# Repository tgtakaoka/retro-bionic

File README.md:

<div align="center">

# retro-bionic

**Run real vintage CPUs on a modern Cortex-M7 — with a debugger, assembler and disassembler built in.**

</div>

## Contents

- [CPUs](docs/supported-cpus.md) — every target supported and planned, with the variants each detects
- [Hardware](docs/hardware.md) — the board stack, signal naming and the awkward chips
- [3.3 V base](docs/3v3-base.md) — planned second base board, its keying and what it unlocks
- [Debugger](docs/debugger.md) — full command reference
- [Build & run](docs/build.md) — toolchain, flashing, serial ports
- [Samples](docs/samples.md) — the programs and how to run them
- [CPU speed by an assembly-language Mandelbrot](docs/mandelbrot.md) — the benchmark's seconds per frame on each chip
- [Demos](docs/demos.md) — recorded terminal sessions, and what to watch for in them

## What is this?

Put a real MC6809, Z80, TMS9900 or CDP1802 into a ZIF socket and single-step it, one bus
cycle at a time, from a terminal on your desk.

**Bionic** runs *genuine* vintage processors — not emulations of them. A
[Teensy 4.1](https://www.pjrc.com/store/teensy41.html) is wired to every pin of the target
CPU and drives the whole system around it: the clock, every bus cycle, and the memory and
peripherals the chip thinks it is talking to. One firmware image — about 470 kB including
every assembler, disassembler and debugger — covers all **57 supported targets**, and the
board tells the controller which one it is.

<div align="center">

</div>

The hardware is two boards:

1. **Base** — the Teensy 4.1, five TXS0108E level shifters for 3.3 V ↔ 5 V translation, data
   bus holders, the 48-pin ZIF socket and the HALT/RUN switch.
2. **CPU adapter** — one small board per processor, holding little more than the chip
   itself, its identity EEPROM and whatever power the part demands. The TMS9900 board, for
   example, generates its own +12 V and −5 V rails and a non-overlapping four-phase clock, and CPUs with
   large address spaces carry an address bus multiplexer.

The 48 signals crossing the connector are named `P10`–`P57`, and each CPU board maps them to
its own pinout in a small TOML file. See **[docs/hardware.md](docs/hardware.md)**.

## Debugger features

- **Single-step a physical CPU** and print every bus cycle it performed (`S`).
- **Live disassembly** of the next instruction after each register dump, via
  [libasm](https://github.com/tgtakaoka/libasm).
- **Registers** read back by injecting instructions and capturing the resulting cycles —
  read and write them (`r`, `=`).
- **Breakpoints**, up to 4 plus one temporary for run-until-address (`B`, `b`, `g`).
- **Memory** dump and patch, separate program and data spaces for Harvard architectures
  (`d`, `p`, `m`, `M`), plus a write-protect area on targets that need one (`P`).
- **Upload** Intel HEX or Motorola S-record straight over the serial link (`U`).
- **Emulated peripherals** — MC6850 ACIA and i8251 USART — and on-chip serial ports of MCU
  targets bridged to your terminal (`I`).
- **Disk images on the SD card** behind emulated disk controllers (`L`, `O`), enough to
  boot [CP/M 2.2, CP/M-86, CP/M-68K, NitrOS-9, Unix V6 and 2.11BSD](docs/samples.md#operating-systems).
- **Automatic board identification** from a UNI/O serial EEPROM, plus **runtime variant
  detection**: one 6502 board reports `MOS6502`, `G65SC02`, `R65C02`, `W65C02S` or
  `W65C816S` depending on which die actually responds.

<div align="center">

<br><em>A <a href="samples/tms9900/mandelbrot.cast">real TMS9900 session</a>: registers,
disassembly, single-stepping with the bus trace, then drawing the Mandelbrot set.</em>
</div>

## Supported CPUs

All 58 targets, grouped by vendor and architecture:

<table>
<thead>
<tr><th>Vendor</th><th>Architecture</th><th>Targets</th></tr>
</thead>
<tbody>
<tr><td rowspan="6">Motorola</td><td>6800</td><td>MC6800 <em>MB8861</em>, MC6801 <em>HD6301</em>, MC6802 <em>MB8870</em>, MC68HC11A, MC68HC11D</td></tr>
<tr><td>6805</td><td>MC146805E2, MC68HC05C0, MC68HC08AZ0</td></tr>
<tr><td>6809</td><td>MC6809 <em>HD6309</em>, MC6809E <em>HD6309E</em></td></tr>
<tr><td>68HC12</td><td>MC68HC12B, MC9S12D, MC9S12X</td></tr>
<tr><td>68HC16</td><td>MC68HC16Z</td></tr>
<tr><td>68000</td><td>MC68008P, MC68008FN, MC68000P <em>MC68HC000, MC68010</em>, MC68000FN <em>MC68HC001, MC68010</em></td></tr>
<tr><td>MOS Technology</td><td>6502</td><td>MOS6502 <em>G65SC02, R65C02, W65C02S, W65C816S</em></td></tr>
<tr><td rowspan="6">Zilog</td><td>Z80</td><td>Z80, NSC800, KL5C80A12</td></tr>
<tr><td>Z180</td><td>Z180, HD64180S</td></tr>
<tr><td>Z280</td><td>Z280</td></tr>
<tr><td>Z380</td><td>Z380</td></tr>
<tr><td>Z8000</td><td>Z8001, Z8002</td></tr>
<tr><td>Z8</td><td>Z86C91, Z88C00</td></tr>
<tr><td rowspan="5">Intel</td><td>MCS-48</td><td>P8039 <em>MSM80C39</em></td></tr>
<tr><td>MCS-51</td><td>P8051 <em>P80C51</em></td></tr>
<tr><td>MCS-80/85</td><td>P8080, P8085</td></tr>
<tr><td>x86</td><td>P8086 <em>P8088, V30, V20</em>, D8087</td></tr>
<tr><td>MCS-96</td><td>P8095BH, N8097BH, S80C196KC, S80296SA</td></tr>
<tr><td rowspan="4">Texas Instruments</td><td>TMS9900</td><td>TMS9900, TMS9980, TMS9981, TMS9995, TMS99105 <em>TMS99110</em></td></tr>
<tr><td>TMS7000</td><td>TMS7000 <em>TMS7001, TMS7001NL4, TMS7002, TMS70C00, TMS70C02</em></td></tr>
<tr><td>TMS370</td><td>TMS370Cx5x</td></tr>
<tr><td>TMS320</td><td>TMS320C15</td></tr>
<tr><td rowspan="2">DEC</td><td>PDP-8</td><td>IM6100, HD6120</td></tr>
<tr><td>PDP-11</td><td>DCT11, DCJ11</td></tr>
<tr><td>RCA</td><td>COSMAC</td><td>CDP1802 <em>CDP1804A</em></td></tr>
<tr><td>Fairchild</td><td>F8</td><td>F3850</td></tr>
<tr><td rowspan="2">National</td><td>SC/MP II</td><td>INS8060</td></tr>
<tr><td>SC/MP III</td><td>INS8070</td></tr>
<tr><td>Signetics</td><td>2650</td><td>SCN2650</td></tr>
<tr><td>Toshiba</td><td>TLCS-90</td><td>TMP90C802</td></tr>
<tr><td>Hitachi</td><td>H16</td><td>HD641016</td></tr>
<tr><td>Panafacom</td><td>MN1610</td><td>MN1613 <em>MN1613A</em></td></tr>
<tr><td>General Instrument</td><td>CP1600</td><td>CP1610</td></tr>
</tbody>
</table>

Targets in *italics* are variants the firmware identifies at runtime, by executing
instructions that behave differently on each die — not by anything written on the board.

See **[docs/supported-cpus.md](docs/supported-cpus.md)** for the full table, including the
CPUs still to be supported.

## Repository layout

| Path | Contents |
|---|---|
| [`debugger/`](debugger) | Teensy 4.1 firmware — shared framework plus 30 per-family back ends |
| [`schematics/`](schematics) | KiCad projects: base, mezzanine, PLCC adapter and 54 CPU adapter boards, with gerbers and PDFs |
| [`pinout/`](pinout) | Pin-map definitions consumed by [dip](https://github.com/tgtakaoka/dip) |
| [`samples/`](samples) | Test programs — Mandelbrot, arithmetic suites, serial echo — ported to every CPU |
| [`scripts/`](scripts) | Bench control, regression, cycle recording and timing scripts, and the PlatformIO `compile_commands.json` helper |

## Related projects

| Project | Role |
|---|---|
| [**libasm**](https://github.com/tgtakaoka/libasm) | The assembler and disassembler engine — 41 architectures, 119 CPU variants, small enough to run on an AVR |
| [**libcli**](https://github.com/tgtakaoka/libcli) | The serial command-line front end the debugger is built on |
| [**dip**](https://github.com/tgtakaoka/dip) | Draws the pinout diagrams from the TOML files in [`pinout/`](pinout) |

## Resources

- **Recorded sessions** — [asciinema.org/~tgtakaoka](https://asciinema.org/~tgtakaoka)
- **Progress log** — [Bluesky](https://bsky.app/profile/tgtakaoka.bsky.social) ·
  [X](https://x.com/tgtakaoka)

## License

Licensed under the [Apache License, Version 2.0](LICENSE.md).

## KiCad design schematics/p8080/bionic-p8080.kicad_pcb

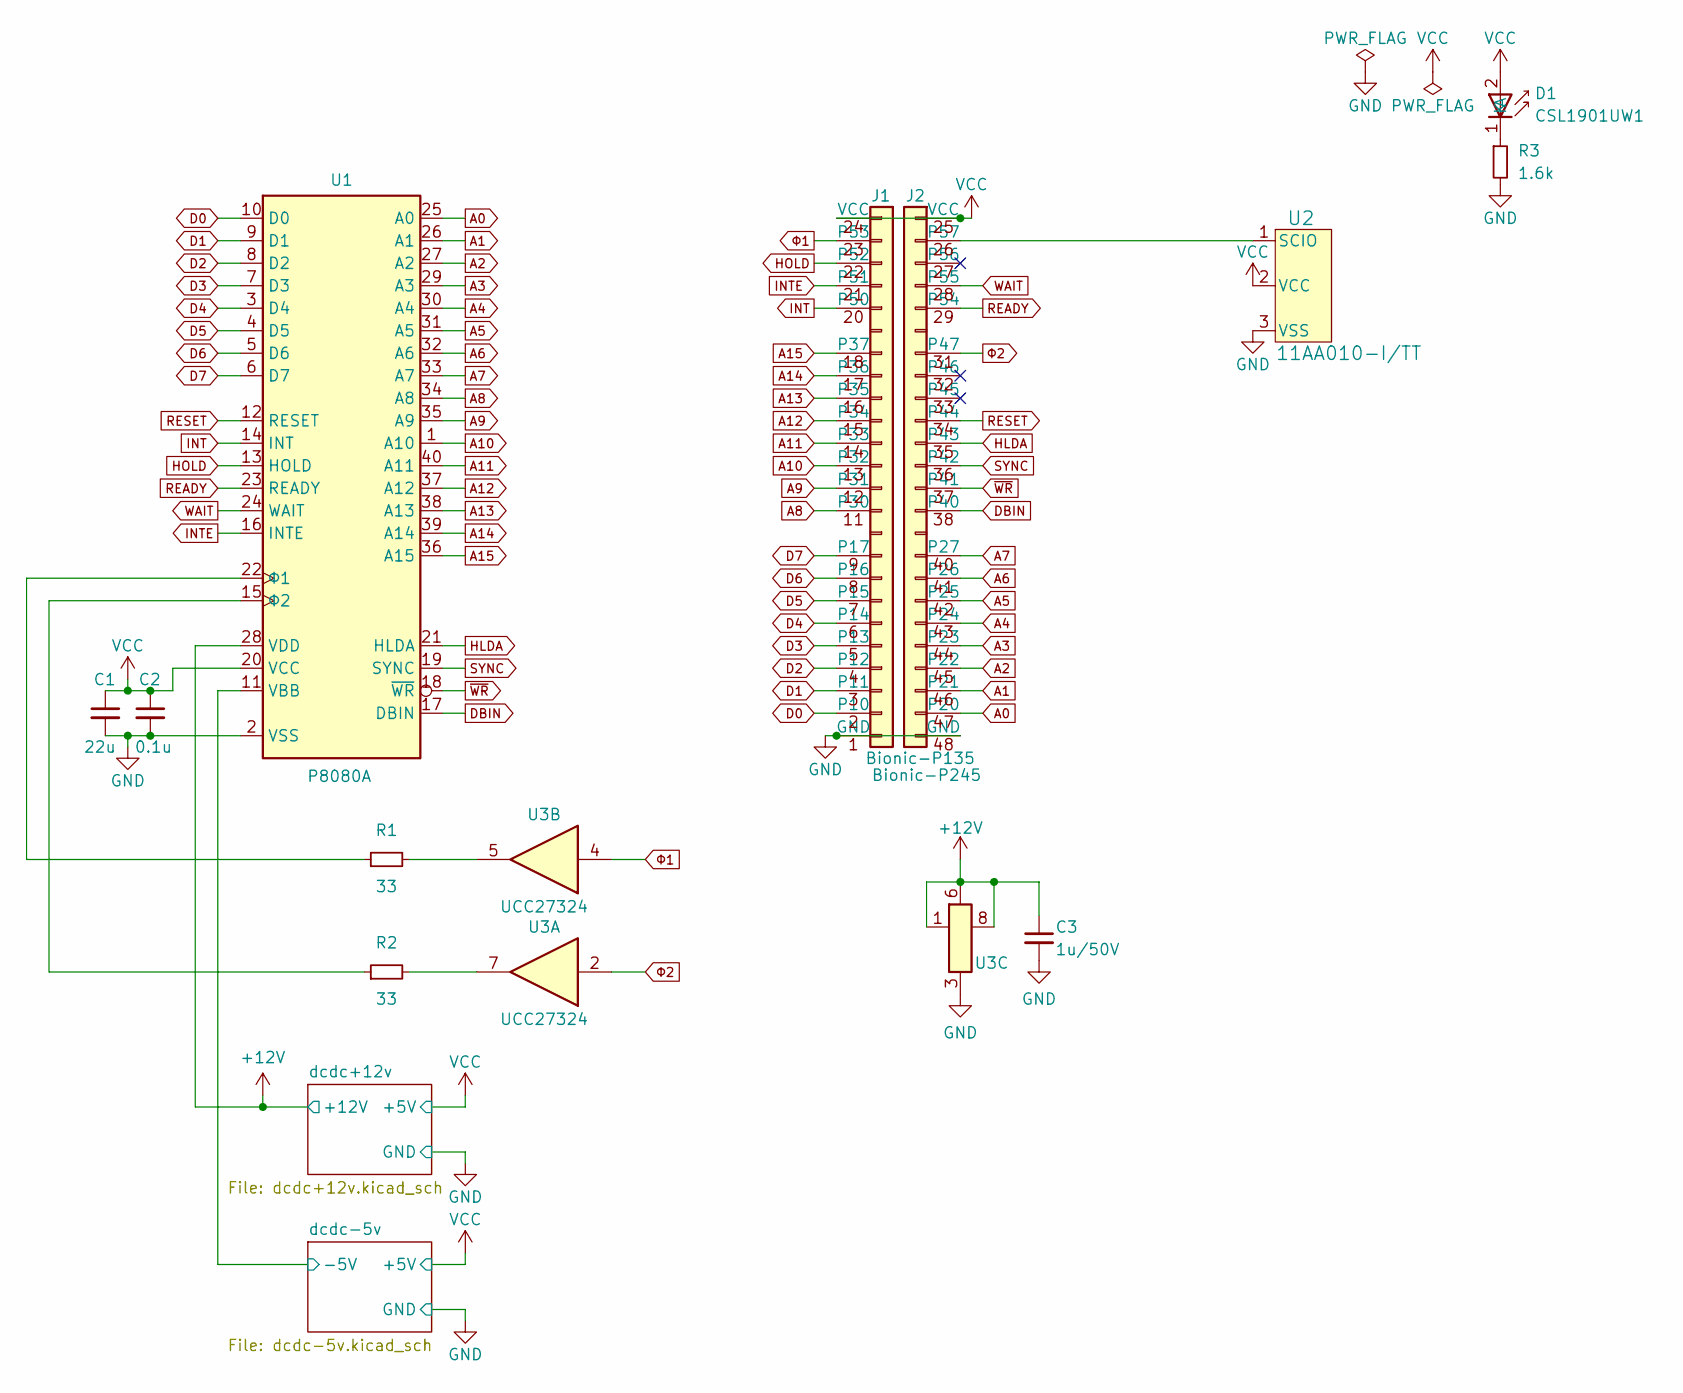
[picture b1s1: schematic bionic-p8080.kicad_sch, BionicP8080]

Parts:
C1: 22u; C_0603_1608Metric_Pad1.08x0.95mm_HandSolder
C2: 0.1u; C_0603_1608Metric_Pad1.08x0.95mm_HandSolder
C3: 1u/50V; C_0603_1608Metric_Pad1.08x0.95mm_HandSolder
D1: CSL1901UW1; LED_CSL1901UW1_ROM-M
J1: Bionic-P135; Bionic-P135_SMT
J2: Bionic-P245; Bionic-P245_SMT
R1, R2: 33; R_0603_1608Metric_Pad0.98x0.95mm_HandSolder
R3: 1.6k; R_0603_1608Metric_Pad0.98x0.95mm_HandSolder
U1: P8080A; DIP-40_W15.24mm_Socket
U2: 11AA010-I/TT; SOT-23_MC_MCH-M
U3: UCC27324; DGN8-M

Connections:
+12V: C3.1, U1.28 (VDD), U3.1 (NC), U3.6 (VDD), U3.8 (NC); also elsewhere on the board
/dcdc-5v/-5V: U1.11 (VBB); also elsewhere on the board
A0: J2.47 (P20), U1.25 (A0)
A1: J2.46 (P21), U1.26 (A1)
A2: J2.45 (P22), U1.27 (A2)
A3: J2.44 (P23), U1.29 (A3)
A4: J2.43 (P24), U1.30 (A4)
A5: J2.42 (P25), U1.31 (A5)
A6: J2.41 (P26), U1.32 (A6)
A7: J2.40 (P27), U1.33 (A7)
A8: J1.11 (P30), U1.34 (A8)
A9: J1.12 (P31), U1.35 (A9)
A10: J1.13 (P32), U1.1 (A10)
A11: J1.14 (P33), U1.40 (A11)
A12: J1.15 (P34), U1.37 (A12)
A13: J1.16 (P35), U1.38 (A13)
A14: J1.17 (P36), U1.39 (A14)
A15: J1.18 (P37), U1.36 (A15)
D0: J1.2 (P10), U1.10 (D0)
D1: J1.3 (P11), U1.9 (D1)
D2: J1.4 (P12), U1.8 (D2)
D3: J1.5 (P13), U1.7 (D3)
D4: J1.6 (P14), U1.3 (D4)
D5: J1.7 (P15), U1.4 (D5)
D6: J1.8 (P16), U1.5 (D6)
D7: J1.9 (P17), U1.6 (D7)
DBIN: J2.38 (P40), U1.17 (DBIN)
GND: C1.2, C2.2, C3.2, J1.1 (GND), J2.48 (GND), R3.2, U1.2 (VSS), U2.3 (VSS), U3.3 (GND); also elsewhere on the board
HLDA: J2.35 (P43), U1.21 (HLDA)
HOLD: J1.22 (P52), U1.13 (HOLD)
INT: J1.20 (P50), U1.14 (INT)
INTE: J1.21 (P51), U1.16 (INTE)
unnamed: D1.1 (K), R3.1
unnamed: J2.26 (P57), U2.1 (SCIO)
unnamed: R1.1, U1.22 (Φ1)
unnamed: R2.1, U1.15 (Φ2)
unnamed: R2.2, U3.7 (OUTA)
unnamed: R1.2, U3.5 (OUTB)
READY: J2.29 (P54), U1.23 (READY)
RESET: J2.34 (P44), U1.12 (RESET)
SYNC: J2.36 (P42), U1.19 (SYNC)
VCC: C1.1, C2.1, D1.2 (A), J1.24 (VCC), J2.25 (VCC), U1.20 (VCC), U2.2 (VCC); also elsewhere on the board
WAIT: J2.28 (P55), U1.24 (WAIT)
~WR: J2.37 (P41), U1.18 (~WR)
Φ1: J1.23 (P53), U3.4 (INB)
Φ2: J2.31 (P47), U3.2 (INA)

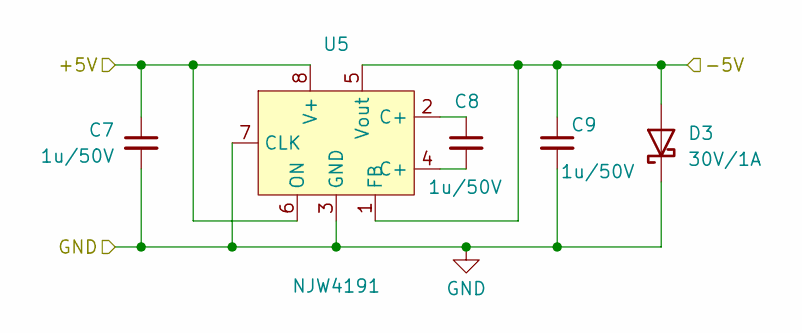
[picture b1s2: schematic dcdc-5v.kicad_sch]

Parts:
C7, C8, C9: 1u/50V; C_0603_1608Metric_Pad1.08x0.95mm_HandSolder
D3: 30V/1A; CR_60M-60_ROM-M
U5: NJW4191; MSOP8VSP8_PI-VSP8-E-B_NMD-M

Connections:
/dcdc-5v/-5V: C9.1, D3.2 (A), U5.1 (FB), U5.5 (Vout); also elsewhere on the board
GND: C7.2, C9.2, D3.1 (K), U5.3 (GND), U5.7 (CLK); also elsewhere on the board
unnamed: C8.1, U5.2 (C+)
unnamed: C8.2, U5.4 (C+)
VCC: C7.1, U5.6 (ON), U5.8 (V+); also elsewhere on the board

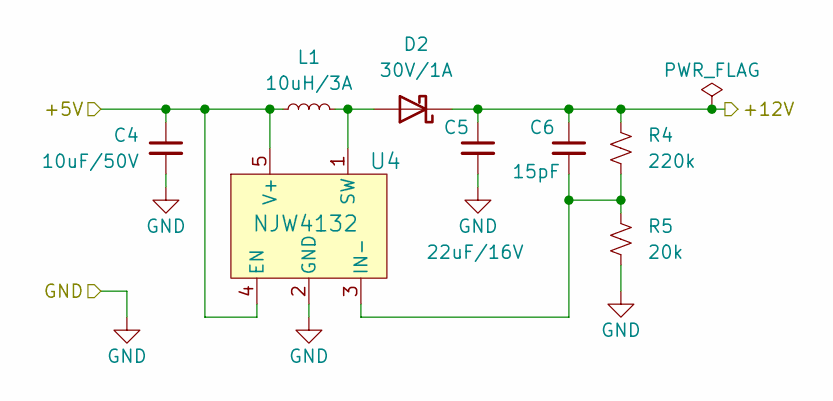
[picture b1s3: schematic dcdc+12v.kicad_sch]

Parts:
C4: 10uF/50V; C_1210_3225Metric_Pad1.33x2.70mm_HandSolder
C5: 22uF/16V; C_1210_3225Metric_Pad1.33x2.70mm_HandSolder
C6: 15pF; C_0603_1608Metric_Pad1.08x0.95mm_HandSolder
D2: 30V/1A; CR_60M-60_ROM-M
L1: 10uH/3A; IND_DFE322512F_MUR-M
R4: 220k; R_0603_1608Metric_Pad0.98x0.95mm_HandSolder
R5: 20k; R_0603_1608Metric_Pad0.98x0.95mm_HandSolder
U4: NJW4132; SOT-89-5_NMD-M

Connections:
+12V: C5.1, C6.1, D2.1 (K), R4.1; also elsewhere on the board
GND: C4.2, C5.2, R5.2, U4.2 (GND); also elsewhere on the board
unnamed: D2.2 (A), L1.2, U4.1 (SW)
unnamed: C6.2, R4.2, R5.1, U4.3 (IN-)
VCC: C4.1, L1.1, U4.4 (EN), U4.5 (V+); also elsewhere on the board

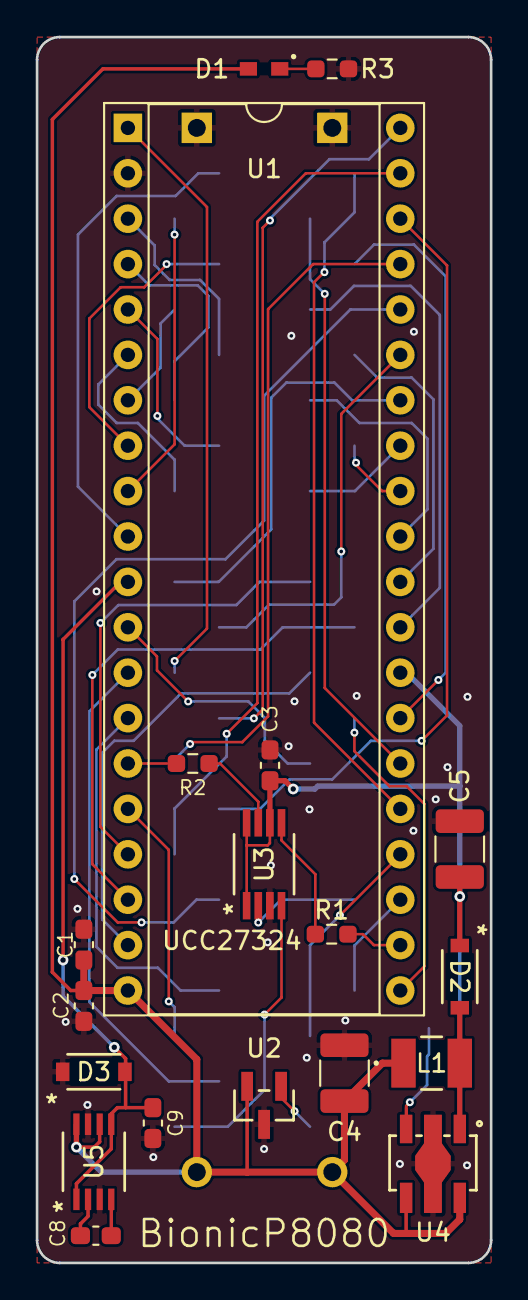
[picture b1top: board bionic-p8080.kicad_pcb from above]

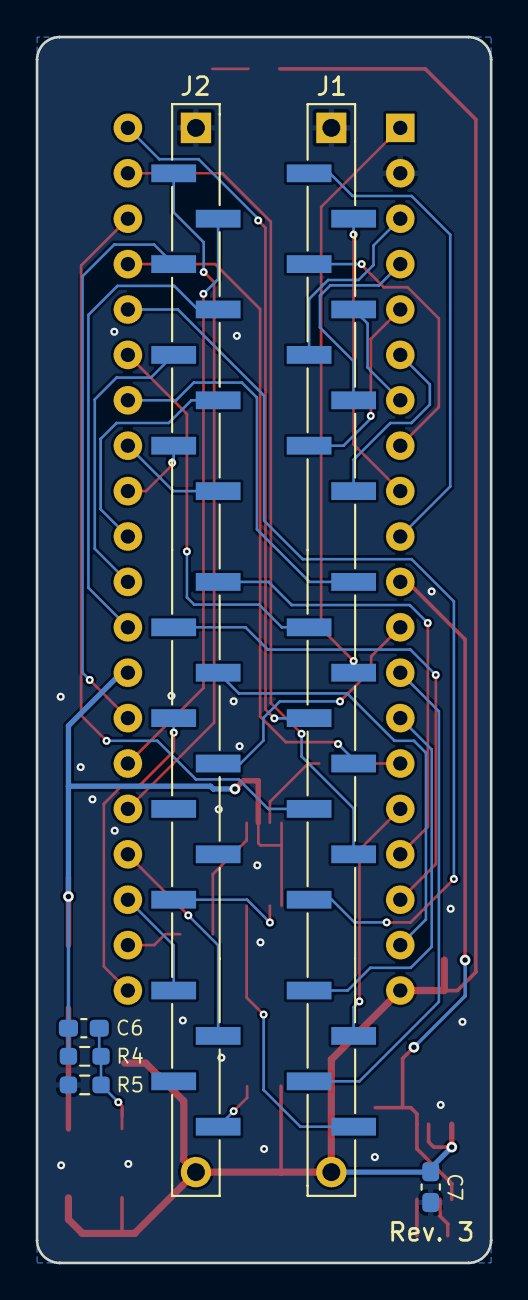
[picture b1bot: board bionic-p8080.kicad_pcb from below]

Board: 2 copper layers, 25.4 x 68.6 mm, 25 parts (6 on the bottom side), 50 nets.

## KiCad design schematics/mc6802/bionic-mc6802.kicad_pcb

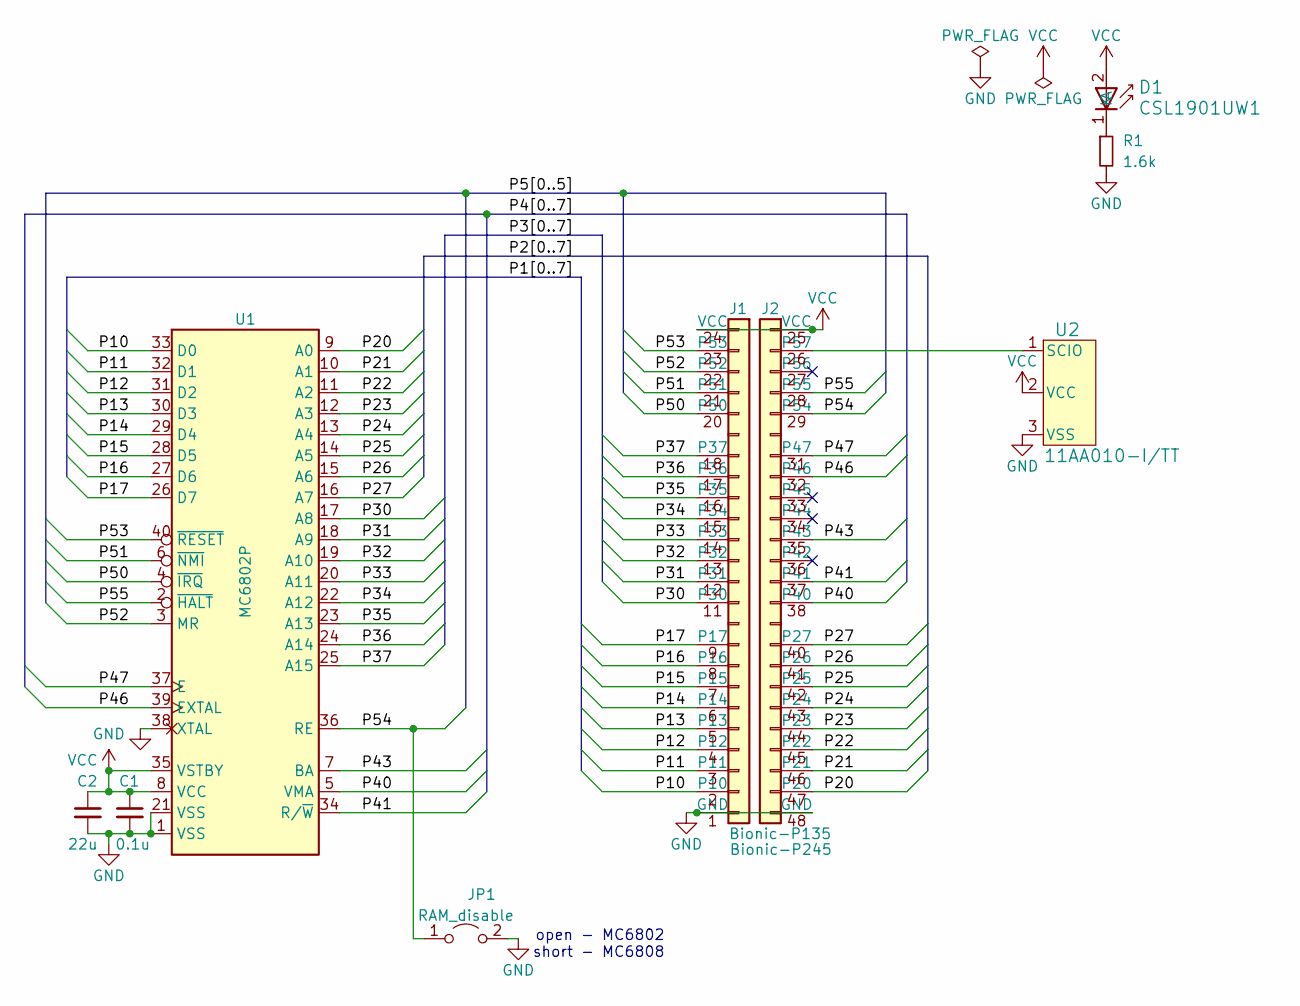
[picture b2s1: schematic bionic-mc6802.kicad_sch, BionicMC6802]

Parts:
C1: 0.1u; C_0603_1608Metric_Pad1.08x0.95mm_HandSolder
C2: 22u; C_0603_1608Metric_Pad1.08x0.95mm_HandSolder
D1: CSL1901UW1; LED_CSL1901UW1_ROM-M
J1: Bionic-P135; Bionic-P135_THT
J2: Bionic-P245; Bionic-P245_THT
JP1: RAM_disable; SolderJumper-2_P1.3mm_Open_RoundedPad1.0x1.5mm
R1: 1.6k; R_0603_1608Metric_Pad0.98x0.95mm_HandSolder
U1: MC6802P; DIP-40_W15.24mm_Socket
U2: 11AA010-I/TT; SOT-23_MC_MCH-M

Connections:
/P10: J1.2 (P10), U1.33 (D0)
/P11: J1.3 (P11), U1.32 (D1)
/P12: J1.4 (P12), U1.31 (D2)
/P13: J1.5 (P13), U1.30 (D3)
/P14: J1.6 (P14), U1.29 (D4)
/P15: J1.7 (P15), U1.28 (D5)
/P16: J1.8 (P16), U1.27 (D6)
/P17: J1.9 (P17), U1.26 (D7)
/P20: J2.47 (P20), U1.9 (A0)
/P21: J2.46 (P21), U1.10 (A1)
/P22: J2.45 (P22), U1.11 (A2)
/P23: J2.44 (P23), U1.12 (A3)
/P24: J2.43 (P24), U1.13 (A4)
/P25: J2.42 (P25), U1.14 (A5)
/P26: J2.41 (P26), U1.15 (A6)
/P27: J2.40 (P27), U1.16 (A7)
/P30: J1.11 (P30), U1.17 (A8)
/P31: J1.12 (P31), U1.18 (A9)
/P32: J1.13 (P32), U1.19 (A10)
/P33: J1.14 (P33), U1.20 (A11)
/P34: J1.15 (P34), U1.22 (A12)
/P35: J1.16 (P35), U1.23 (A13)
/P36: J1.17 (P36), U1.24 (A14)
/P37: J1.18 (P37), U1.25 (A15)
/P40: J2.38 (P40), U1.5 (VMA)
/P41: J2.37 (P41), U1.34 (R/~W)
/P43: J2.35 (P43), U1.7 (BA)
/P46: J2.32 (P46), U1.39 (EXTAL)
/P47: J2.31 (P47), U1.37 (E)
/P50: J1.20 (P50), U1.4 (~IRQ)
/P51: J1.21 (P51), U1.6 (~NMI)
/P52: J1.22 (P52), U1.3 (MR)
/P53: J1.23 (P53), U1.40 (~RESET)
/P54: J2.29 (P54), JP1.1 (A), U1.36 (RE)
/P55: J2.28 (P55), U1.2 (~HALT)
GND: C1.2, C2.2, J1.1 (GND), J2.48 (GND), JP1.2 (B), R1.2, U1.1 (VSS), U1.21 (VSS), U1.38 (XTAL), U2.3 (VSS)
unnamed: D1.1 (K), R1.1
unnamed: J2.26 (P57), U2.1 (SCIO)
VCC: C1.1, C2.1, D1.2 (A), J1.24 (VCC), J2.25 (VCC), U1.8 (VCC), U1.35 (VSTBY), U2.2 (VCC)

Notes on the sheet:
open - MC6802 short - MC6808

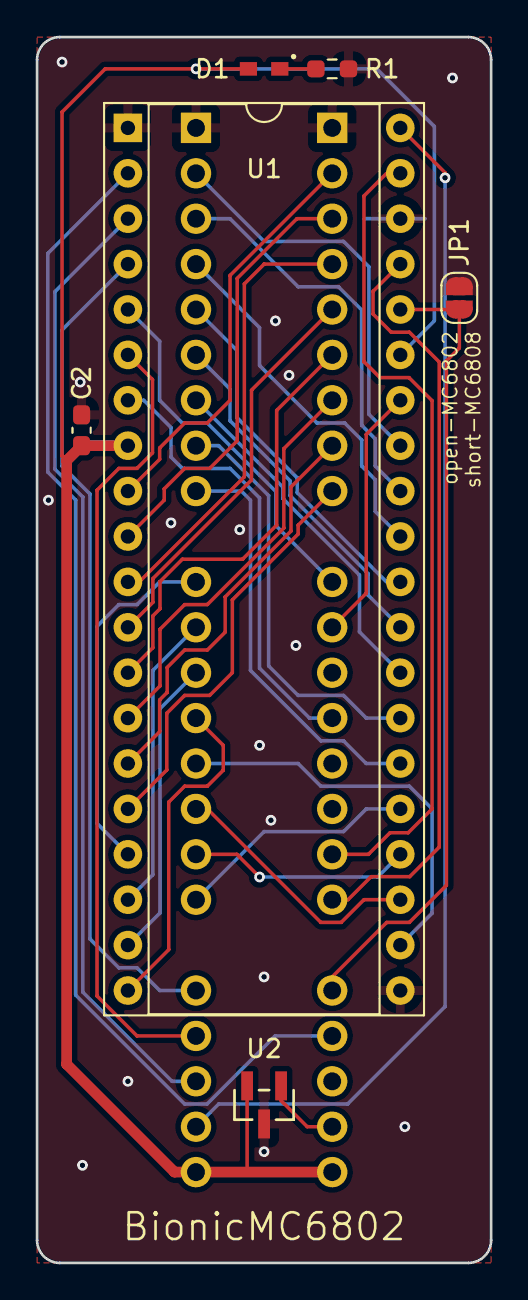
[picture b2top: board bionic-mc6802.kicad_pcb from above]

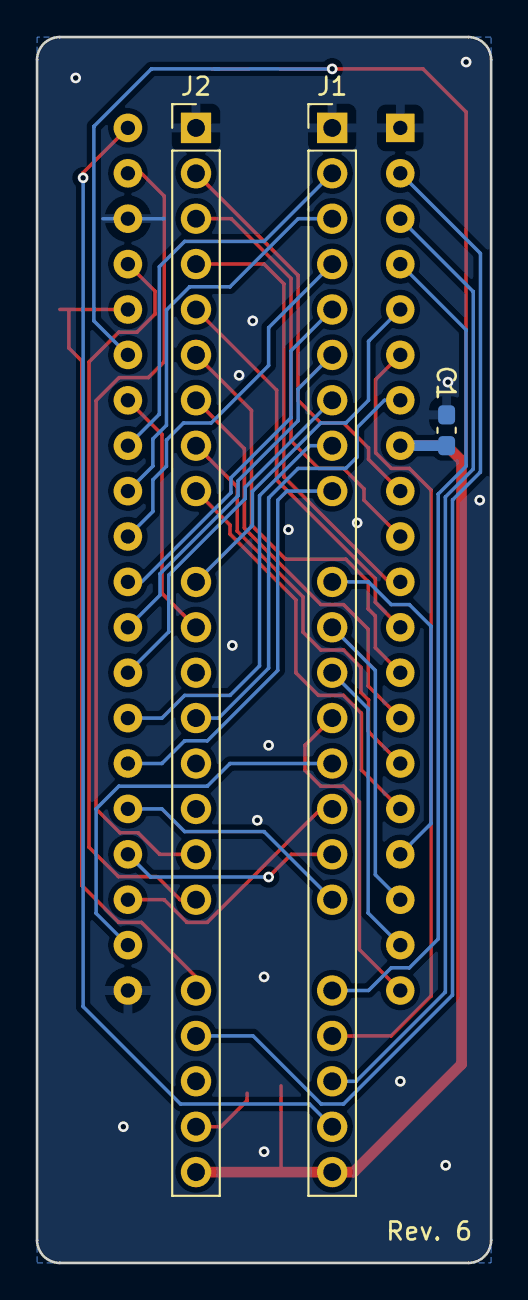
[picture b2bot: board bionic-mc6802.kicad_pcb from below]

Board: 2 copper layers, 25.4 x 68.6 mm, 9 parts (3 on the bottom side), 39 nets.

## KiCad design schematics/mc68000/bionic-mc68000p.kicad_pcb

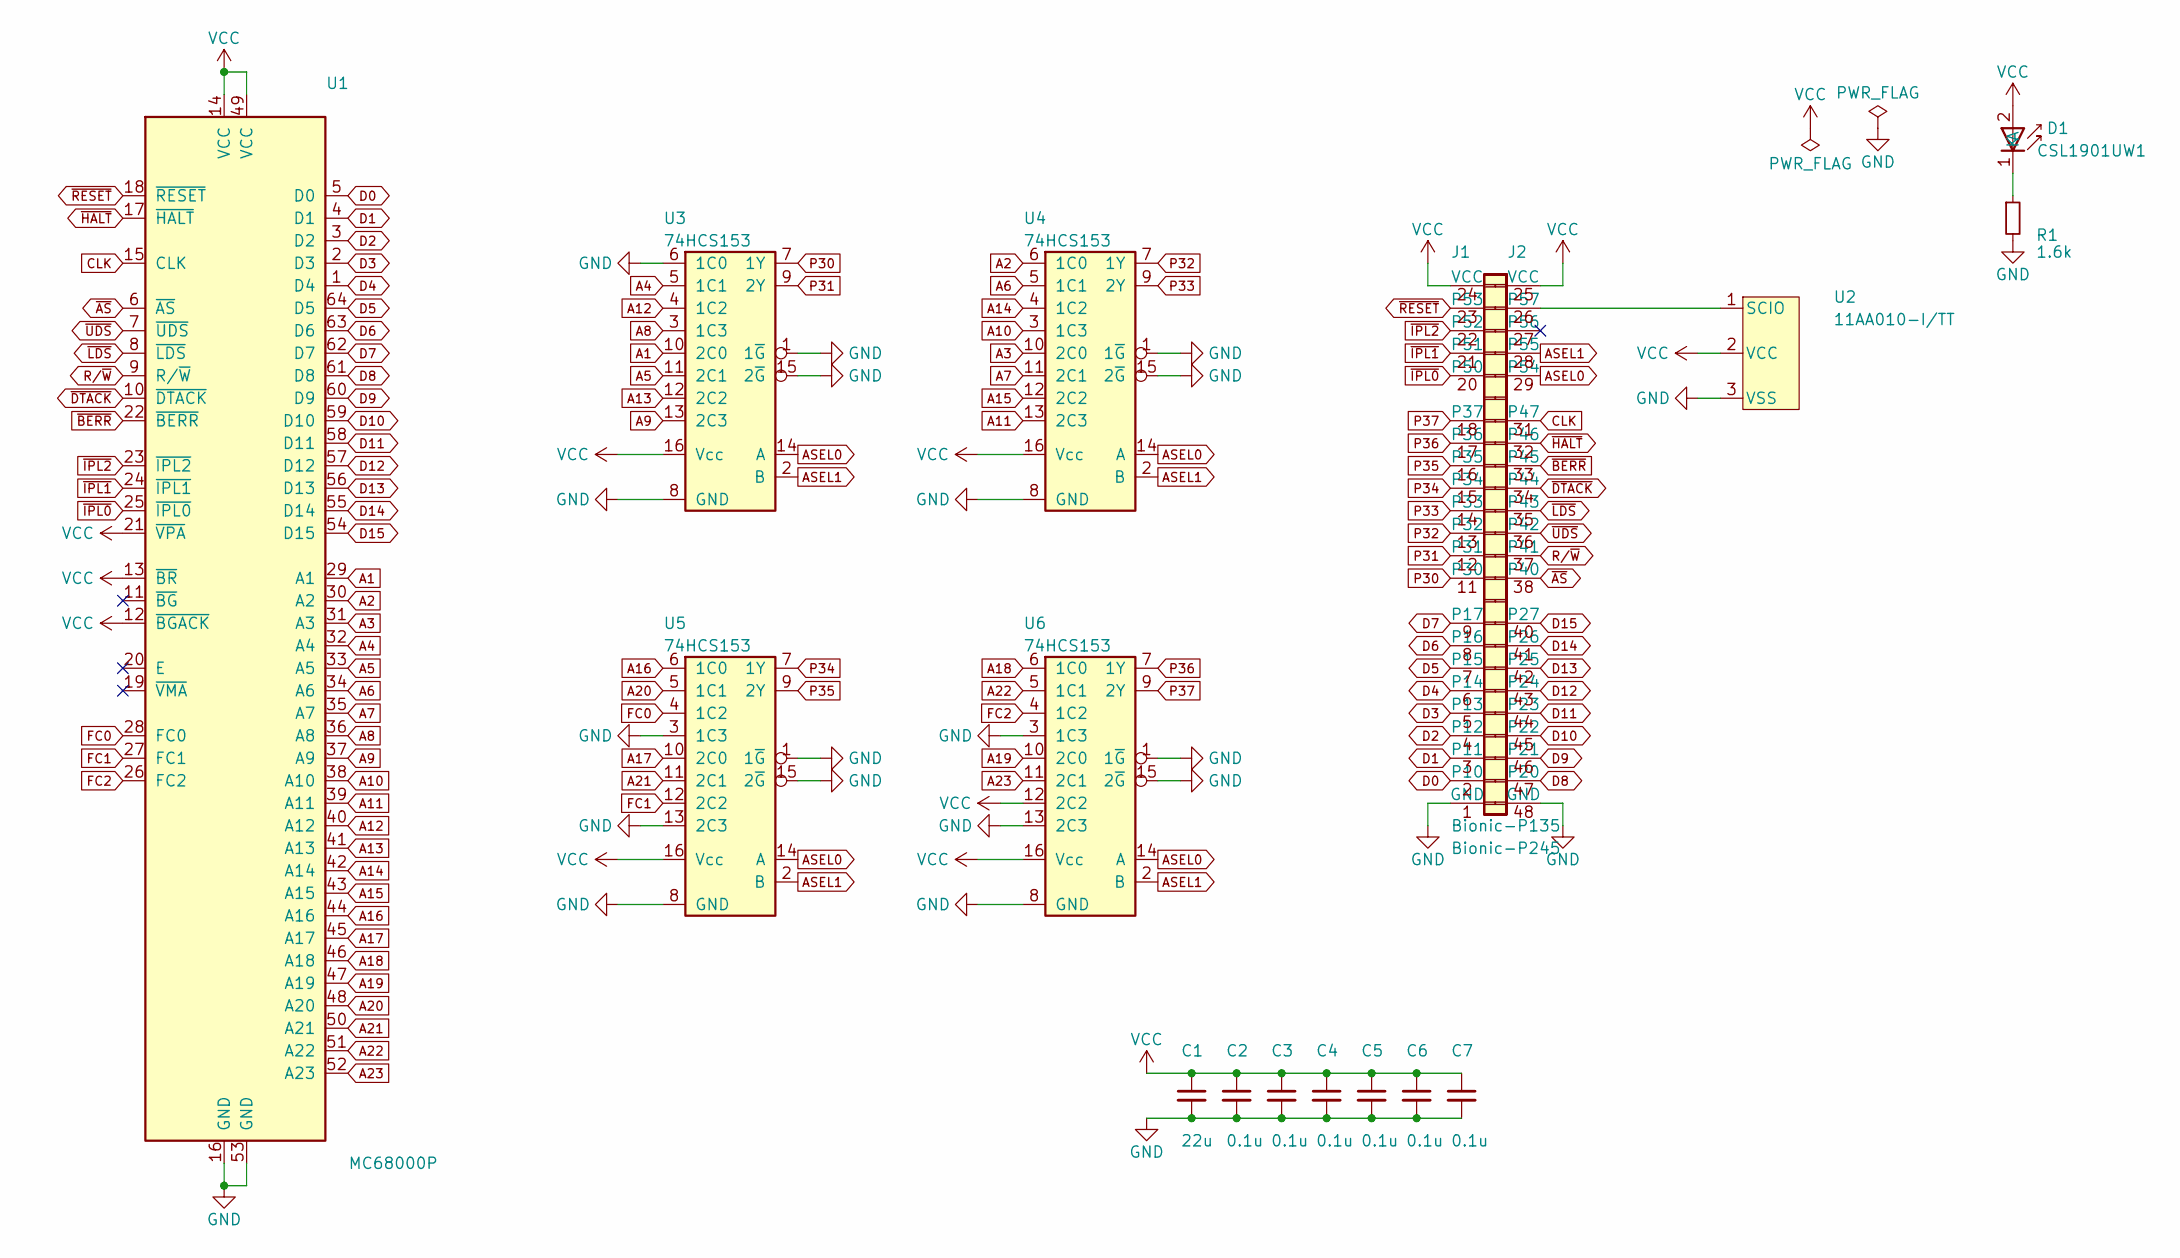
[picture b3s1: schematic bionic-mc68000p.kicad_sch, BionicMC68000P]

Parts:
C1: 22u; C_0603_1608Metric_Pad1.08x0.95mm_HandSolder
C2, C3, C4, C5, C6, C7: 0.1u; C_0603_1608Metric_Pad1.08x0.95mm_HandSolder
D1: CSL1901UW1; LED_CSL1901UW1_ROM-M
J1: Bionic-P135; Bionic-P135_SMT
J2: Bionic-P245; Bionic-P245_SMT
R1: 1.6k; R_0603_1608Metric_Pad0.98x0.95mm_HandSolder
U1: MC68000P; DIP-64_W22.86mm_Socket
U2: 11AA010-I/TT; SOT-23_MC_MCH-M
U3, U4, U5, U6: 74HCS153; PW16-M

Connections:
A1: U1.29 (A1), U3.10 (2C0)
A2: U1.30 (A2), U4.6 (1C0)
A3: U1.31 (A3), U4.10 (2C0)
A4: U1.32 (A4), U3.5 (1C1)
A5: U1.33 (A5), U3.11 (2C1)
A6: U1.34 (A6), U4.5 (1C1)
A7: U1.35 (A7), U4.11 (2C1)
A8: U1.36 (A8), U3.3 (1C3)
A9: U1.37 (A9), U3.13 (2C3)
A10: U1.38 (A10), U4.3 (1C3)
A11: U1.39 (A11), U4.13 (2C3)
A12: U1.40 (A12), U3.4 (1C2)
A13: U1.41 (A13), U3.12 (2C2)
A14: U1.42 (A14), U4.4 (1C2)
A15: U1.43 (A15), U4.12 (2C2)
A16: U1.44 (A16), U5.6 (1C0)
A17: U1.45 (A17), U5.10 (2C0)
A18: U1.46 (A18), U6.6 (1C0)
A19: U1.47 (A19), U6.10 (2C0)
A20: U1.48 (A20), U5.5 (1C1)
A21: U1.50 (A21), U5.11 (2C1)
A22: U1.51 (A22), U6.5 (1C1)
A23: U1.52 (A23), U6.11 (2C1)
ASEL0: J2.29 (P54), U3.14 (A), U4.14 (A), U5.14 (A), U6.14 (A)
ASEL1: J2.28 (P55), U3.2 (B), U4.2 (B), U5.2 (B), U6.2 (B)
CLK: J2.31 (P47), U1.15 (CLK)
D0: J1.2 (P10), U1.5 (D0)
D1: J1.3 (P11), U1.4 (D1)
D2: J1.4 (P12), U1.3 (D2)
D3: J1.5 (P13), U1.2 (D3)
D4: J1.6 (P14), U1.1 (D4)
D5: J1.7 (P15), U1.64 (D5)
D6: J1.8 (P16), U1.63 (D6)
D7: J1.9 (P17), U1.62 (D7)
D8: J2.47 (P20), U1.61 (D8)
D9: J2.46 (P21), U1.60 (D9)
D10: J2.45 (P22), U1.59 (D10)
D11: J2.44 (P23), U1.58 (D11)
D12: J2.43 (P24), U1.57 (D12)
D13: J2.42 (P25), U1.56 (D13)
D14: J2.41 (P26), U1.55 (D14)
D15: J2.40 (P27), U1.54 (D15)
FC0: U1.28 (FC0), U5.4 (1C2)
FC1: U1.27 (FC1), U5.12 (2C2)
FC2: U1.26 (FC2), U6.4 (1C2)
GND: C1.2, C2.2, C3.2, C4.2, C5.2, C6.2, C7.2, J1.1 (GND), J2.48 (GND), R1.2, U1.16 (GND), U1.53 (GND), U2.3 (VSS), U3.1 (1~G), U3.6 (1C0), U3.8 (GND), U3.15 (2~G), U4.1 (1~G), U4.8 (GND), U4.15 (2~G), U5.1 (1~G), U5.3 (1C3), U5.8 (GND), U5.13 (2C3), U5.15 (2~G), U6.1 (1~G), U6.3 (1C3), U6.8 (GND), U6.13 (2C3), U6.15 (2~G)
unnamed: D1.1 (K), R1.1
unnamed: J2.26 (P57), U2.1 (SCIO)
P30: J1.11 (P30), U3.7 (1Y)
P31: J1.12 (P31), U3.9 (2Y)
P32: J1.13 (P32), U4.7 (1Y)
P33: J1.14 (P33), U4.9 (2Y)
P34: J1.15 (P34), U5.7 (1Y)
P35: J1.16 (P35), U5.9 (2Y)
P36: J1.17 (P36), U6.7 (1Y)
P37: J1.18 (P37), U6.9 (2Y)
R/~W: J2.37 (P41), U1.9 (R/~W)
VCC: C1.1, C2.1, C3.1, C4.1, C5.1, C6.1, C7.1, D1.2 (A), J1.24 (VCC), J2.25 (VCC), U1.12 (~BGACK), U1.13 (~BR), U1.14 (VCC), U1.21 (~VPA), U1.49 (VCC), U2.2 (VCC), U3.16 (Vcc), U4.16 (Vcc), U5.16 (Vcc), U6.12 (2C2), U6.16 (Vcc)
~AS: J2.38 (P40), U1.6 (~AS)
~BERR: J2.33 (P45), U1.22 (~BERR)
~DTACK: J2.34 (P44), U1.10 (~DTACK)
~HALT: J2.32 (P46), U1.17 (~HALT)
~IPL0: J1.20 (P50), U1.25 (~IPL0)
~IPL1: J1.21 (P51), U1.24 (~IPL1)
~IPL2: J1.22 (P52), U1.23 (~IPL2)
~LDS: J2.35 (P43), U1.8 (~LDS)
~RESET: J1.23 (P53), U1.18 (~RESET)
~UDS: J2.36 (P42), U1.7 (~UDS)

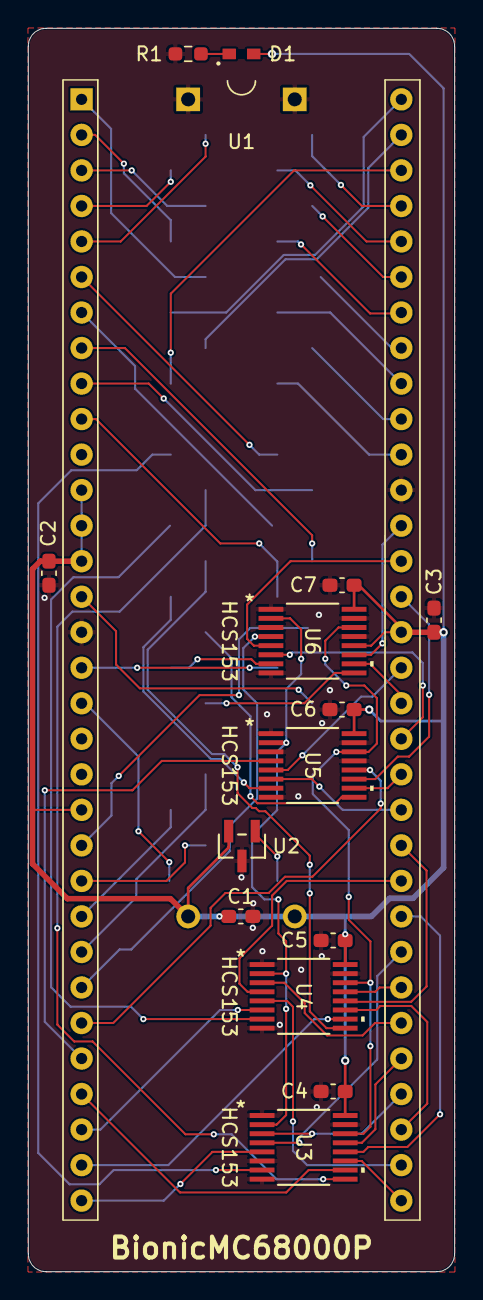
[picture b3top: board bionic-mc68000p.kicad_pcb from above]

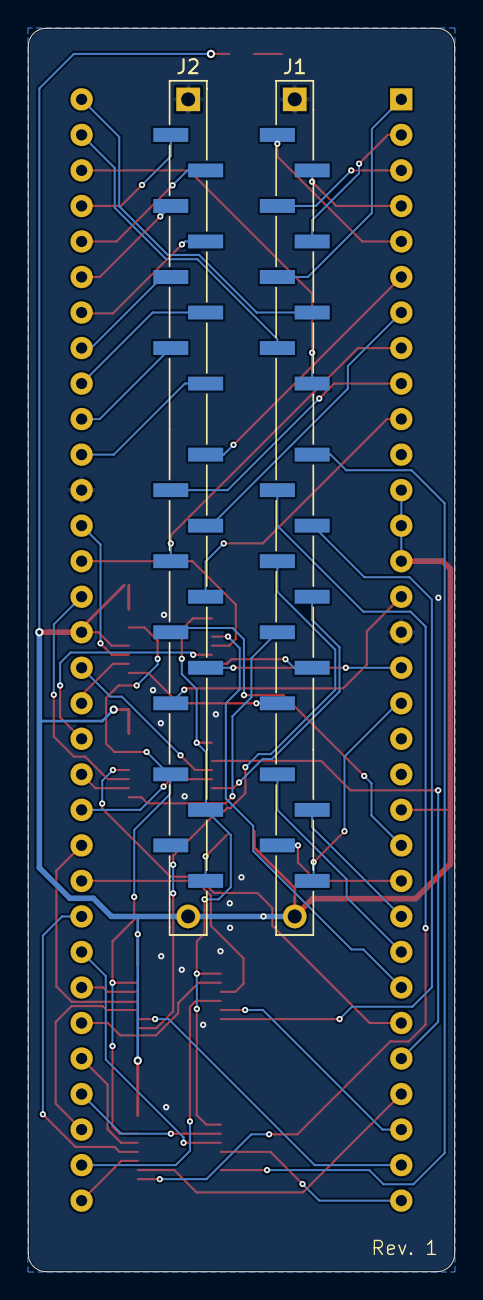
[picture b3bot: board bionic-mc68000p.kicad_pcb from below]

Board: 2 copper layers, 30.5 x 88.9 mm, 17 parts (2 on the bottom side), 68 nets.

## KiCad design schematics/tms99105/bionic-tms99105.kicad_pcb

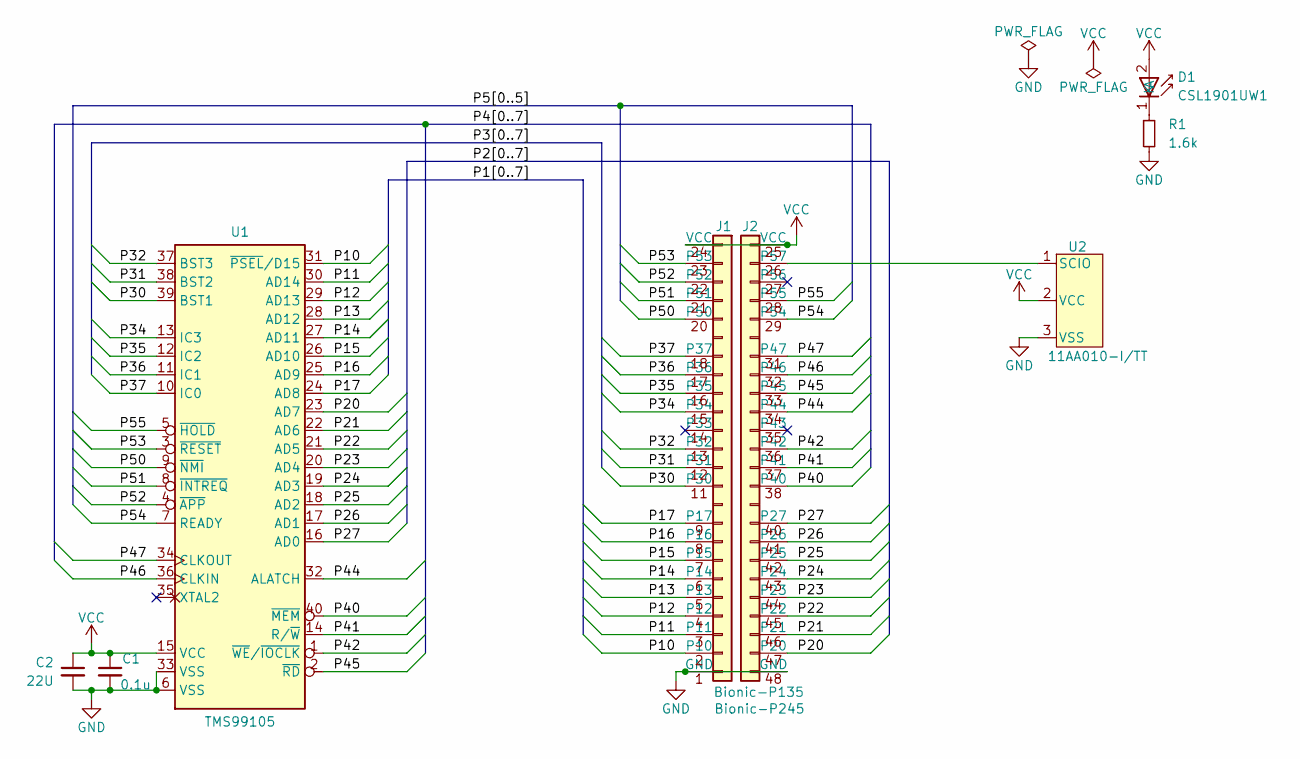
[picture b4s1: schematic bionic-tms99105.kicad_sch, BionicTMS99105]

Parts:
C1: 0.1u; C_0603_1608Metric_Pad1.08x0.95mm_HandSolder
C2: 22U; C_0603_1608Metric_Pad1.08x0.95mm_HandSolder
D1: CSL1901UW1; LED_CSL1901UW1_ROM-M
J1: Bionic-P135; Bionic-P135_THT
J2: Bionic-P245; Bionic-P245_THT
R1: 1.6k; R_0603_1608Metric_Pad0.98x0.95mm_HandSolder
U1: TMS99105; DIP-40_W15.24mm_Socket
U2: 11AA010-I/TT; SOT-23_MC_MCH-M

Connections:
/P10: J1.2 (P10), U1.31 (~PSEL/D15)
/P11: J1.3 (P11), U1.30 (AD14)
/P12: J1.4 (P12), U1.29 (AD13)
/P13: J1.5 (P13), U1.28 (AD12)
/P14: J1.6 (P14), U1.27 (AD11)
/P15: J1.7 (P15), U1.26 (AD10)
/P16: J1.8 (P16), U1.25 (AD9)
/P17: J1.9 (P17), U1.24 (AD8)
/P20: J2.47 (P20), U1.23 (AD7)
/P21: J2.46 (P21), U1.22 (AD6)
/P22: J2.45 (P22), U1.21 (AD5)
/P23: J2.44 (P23), U1.20 (AD4)
/P24: J2.43 (P24), U1.19 (AD3)
/P25: J2.42 (P25), U1.18 (AD2)
/P26: J2.41 (P26), U1.17 (AD1)
/P27: J2.40 (P27), U1.16 (AD0)
/P30: J1.11 (P30), U1.39 (BST1)
/P31: J1.12 (P31), U1.38 (BST2)
/P32: J1.13 (P32), U1.37 (BST3)
/P34: J1.15 (P34), U1.13 (IC3)
/P35: J1.16 (P35), U1.12 (IC2)
/P36: J1.17 (P36), U1.11 (IC1)
/P37: J1.18 (P37), U1.10 (IC0)
/P40: J2.38 (P40), U1.40 (~MEM)
/P41: J2.37 (P41), U1.14 (R/~W)
/P42: J2.36 (P42), U1.1 (~WE/~IOCLK)
/P44: J2.34 (P44), U1.32 (ALATCH)
/P45: J2.33 (P45), U1.2 (~RD)
/P46: J2.32 (P46), U1.36 (CLKIN)
/P47: J2.31 (P47), U1.34 (CLKOUT)
/P50: J1.20 (P50), U1.9 (~NMI)
/P51: J1.21 (P51), U1.8 (~INTREQ)
/P52: J1.22 (P52), U1.4 (~APP)
/P53: J1.23 (P53), U1.3 (~RESET)
/P54: J2.29 (P54), U1.7 (READY)
/P55: J2.28 (P55), U1.5 (~HOLD)
GND: C1.2, C2.2, J1.1 (GND), J2.48 (GND), R1.2, U1.6 (VSS), U1.33 (VSS), U2.3 (VSS)
unnamed: D1.1 (K), R1.1
unnamed: J2.26 (P57), U2.1 (SCIO)
VCC: C1.1, C2.1, D1.2 (A), J1.24 (VCC), J2.25 (VCC), U1.15 (VCC), U2.2 (VCC)

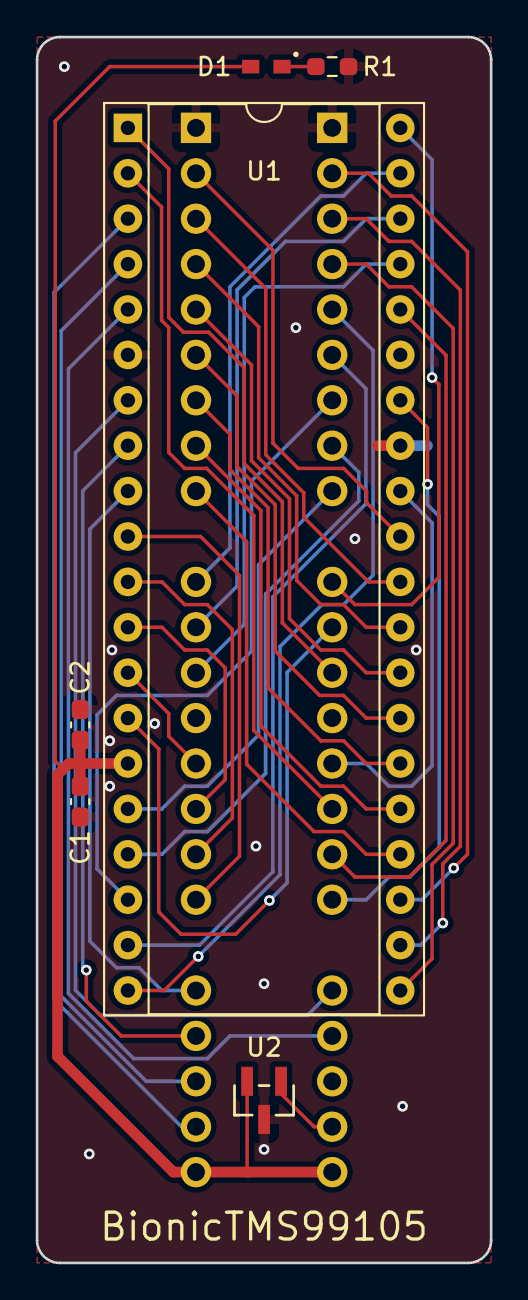
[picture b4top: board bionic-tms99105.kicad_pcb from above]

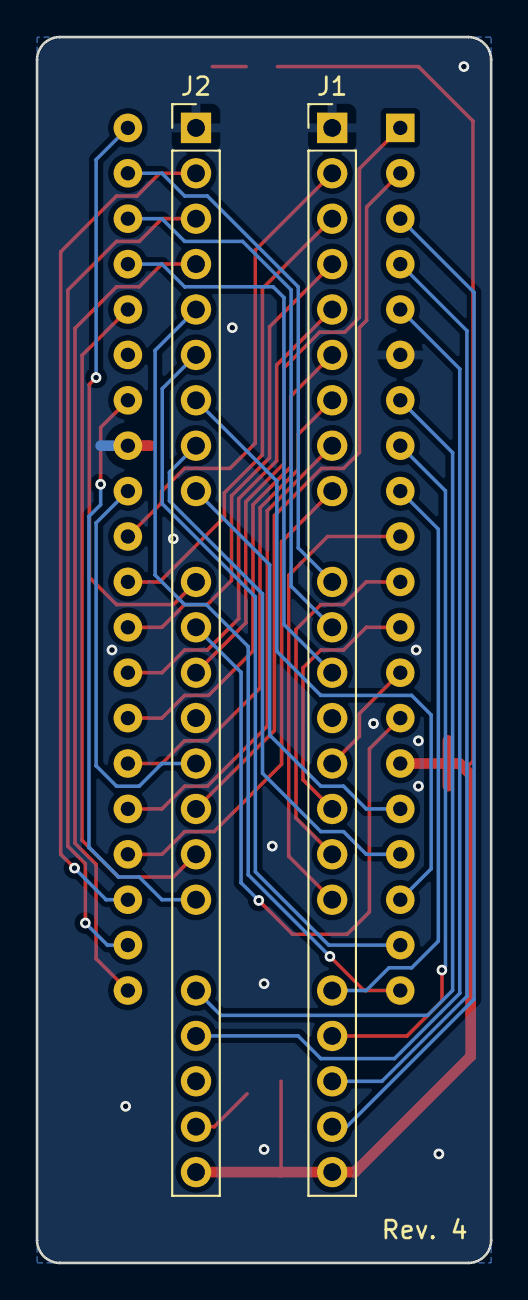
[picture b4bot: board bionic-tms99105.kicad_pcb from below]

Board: 2 copper layers, 25.4 x 68.6 mm, 8 parts (2 on the bottom side), 40 nets.

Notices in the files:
README.md:
License: Apache 2.0
